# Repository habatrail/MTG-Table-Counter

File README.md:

# MTG-Table-Counter
A tabletop companion for TCG and other games, based on RP2040 from Adafruit and circuit python. 

There are also some fonts converted to Bitmaps via font forge saved here as well that are good for use on the feather as they are small files.

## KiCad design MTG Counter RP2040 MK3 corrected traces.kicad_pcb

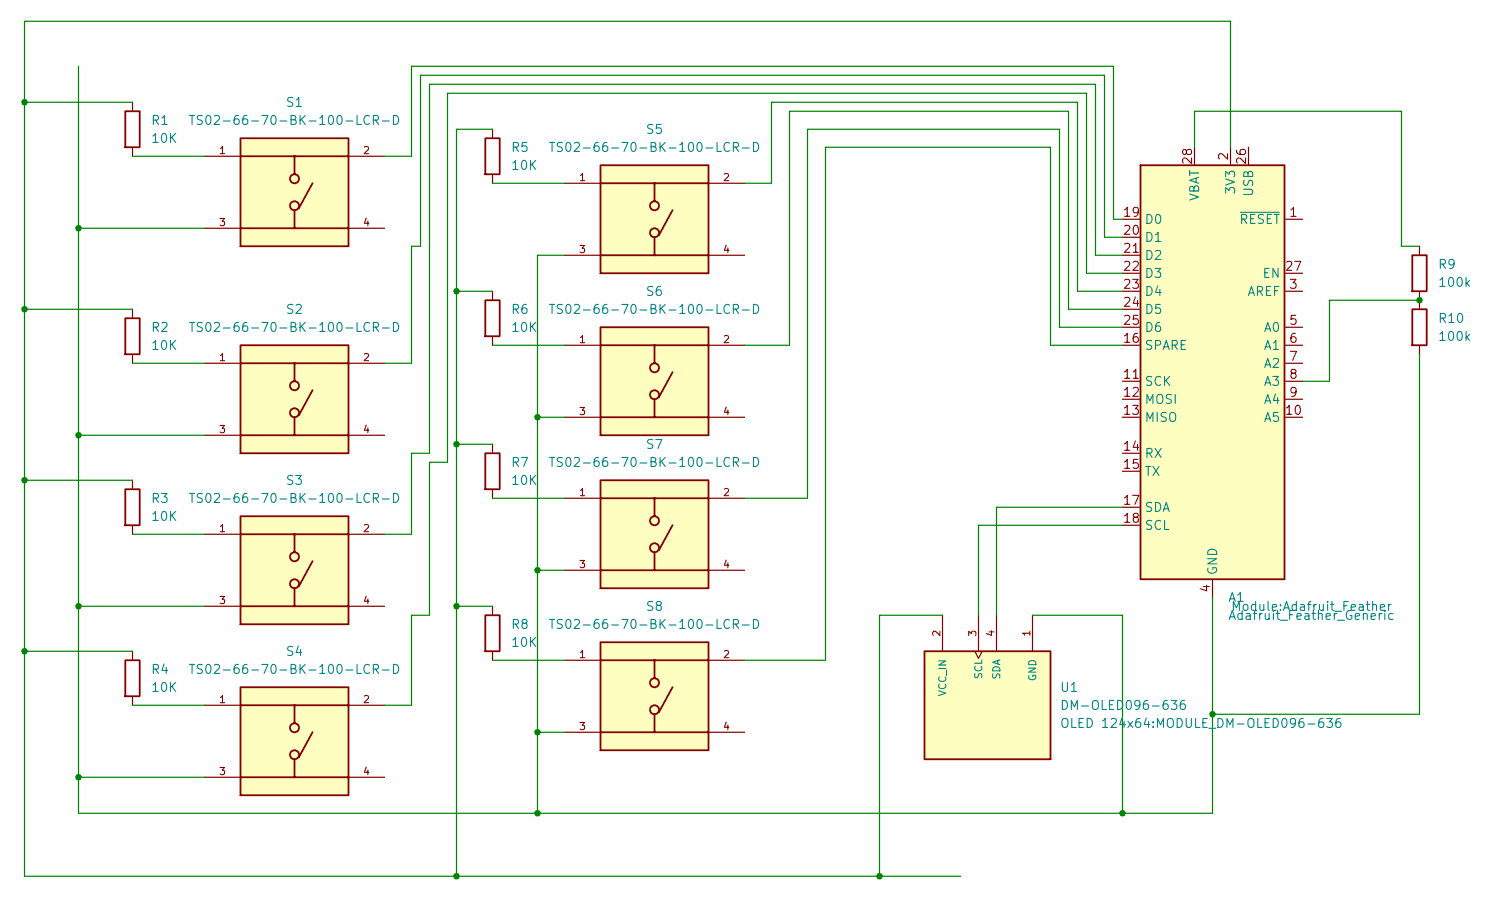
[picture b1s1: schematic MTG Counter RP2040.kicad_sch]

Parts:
A1: Adafruit_Feather_Generic; Adafruit_Feather
R1, R2, R3, R4, R5, R6, R7, R8: 10K; R_Axial_DIN0204_L3.6mm_D1.6mm_P5.08mm_Horizontal
R9, R10: 100k; R_Axial_DIN0204_L3.6mm_D1.6mm_P5.08mm_Horizontal
S1, S2, S3, S4, S5, S6, S7, S8: TS02-66-70-BK-100-LCR-D; SW_PUSH_6mm_H4.3mm(PROPERBUTTON); PARTREV 1.0
U1: DM-OLED096-636; MODULE_DM-OLED096-636; PARTREV 2018-09-10

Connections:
unnamed: A1.2 (3V3), R1.1, R2.1, R3.1, R4.1, R5.1, R6.1, R7.1, R8.1, U1.2 (VCC_IN)
unnamed: A1.8 (A3), R9.2, R10.1
unnamed: A1.19 (D0), S1.2
unnamed: A1.20 (D1), S2.2
unnamed: A1.21 (D2), S3.2
unnamed: A1.22 (D3), S4.2
unnamed: A1.23 (D4), S5.2
unnamed: A1.24 (D5), S6.2
unnamed: A1.25 (D6), S7.2
unnamed: A1.4 (GND), R10.2, S1.3, S2.3, S3.3, S4.3, S5.3, S6.3, S7.3, S8.3, U1.1 (GND)
unnamed: A1.18 (SCL), U1.3 (SCL)
unnamed: A1.17 (SDA), U1.4 (SDA)
unnamed: A1.16 (SPARE), S8.2
unnamed: A1.28 (VBAT), R9.1
unnamed: R1.2, S1.1
unnamed: R2.2, S2.1
unnamed: R3.2, S3.1
unnamed: R4.2, S4.1
unnamed: R5.2, S5.1
unnamed: R6.2, S6.1
unnamed: R7.2, S7.1
unnamed: R8.2, S8.1

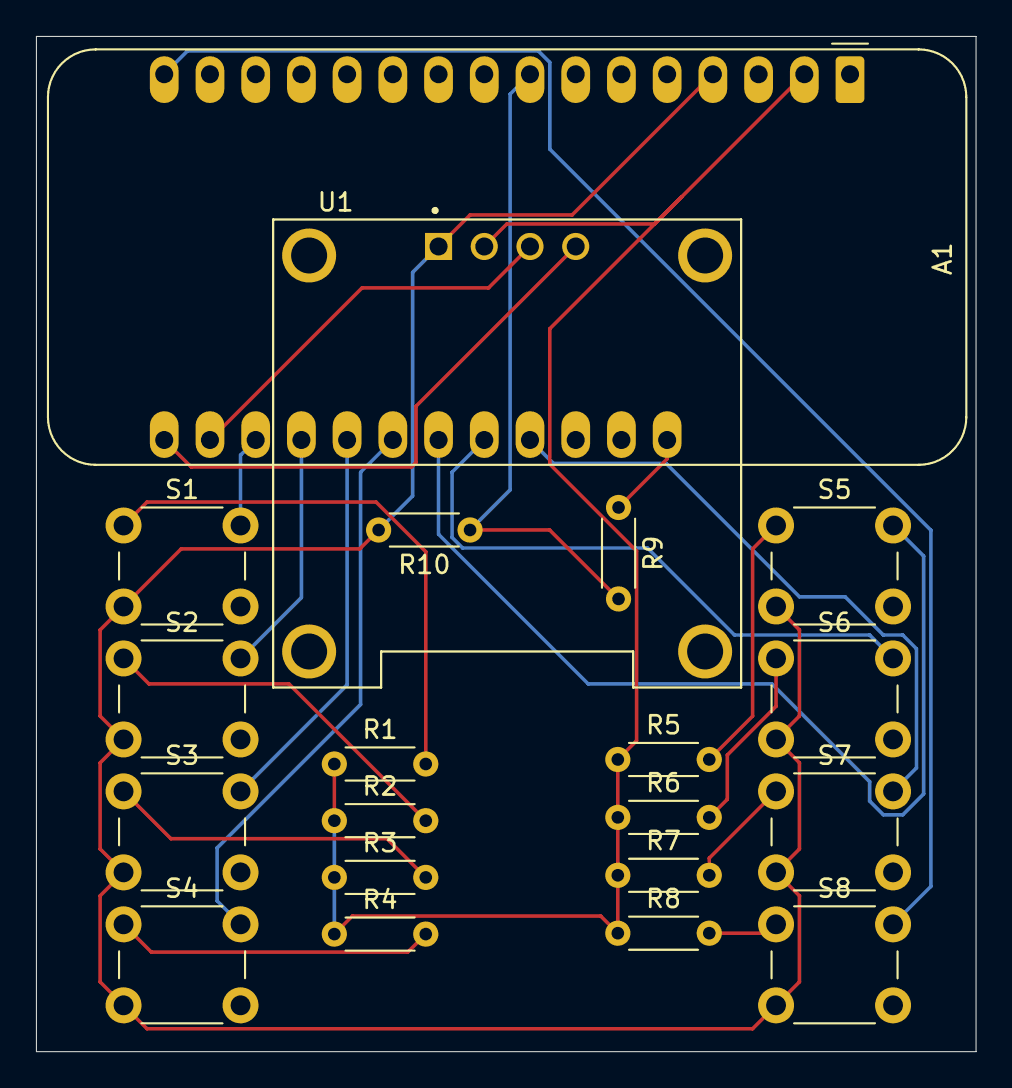
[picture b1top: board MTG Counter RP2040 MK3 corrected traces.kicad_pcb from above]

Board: 2 copper layers, 52.2 x 56.4 mm, 20 parts (0 on the bottom side), 22 nets.

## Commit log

2025-05-20 Current code for the hand held with 128x 64 screen
2025-05-20 Various fonts used in early stages of dev
    all from online sources converted to a format that works with the GFX library.
2025-05-20 Rename code.py to 2025_19_5_primary_code.py
2025-05-20 PCB and Schematic
    KiCad files from the corrected second round of PCBs ordered from JLBPCB
2025-05-31 Step files for completed pcb roughly accurate
    some wiggle room on front display and rp2040 depth needs to be tested.
2025-10-06 Updated code for the main Feater
    This code removed a problematic screensaver section from a previously unpublished version and is relatively stable for table top play.
